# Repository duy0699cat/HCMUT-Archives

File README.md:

# HCMUT-Archives
llaalalala
a;dsuigflaisubgila

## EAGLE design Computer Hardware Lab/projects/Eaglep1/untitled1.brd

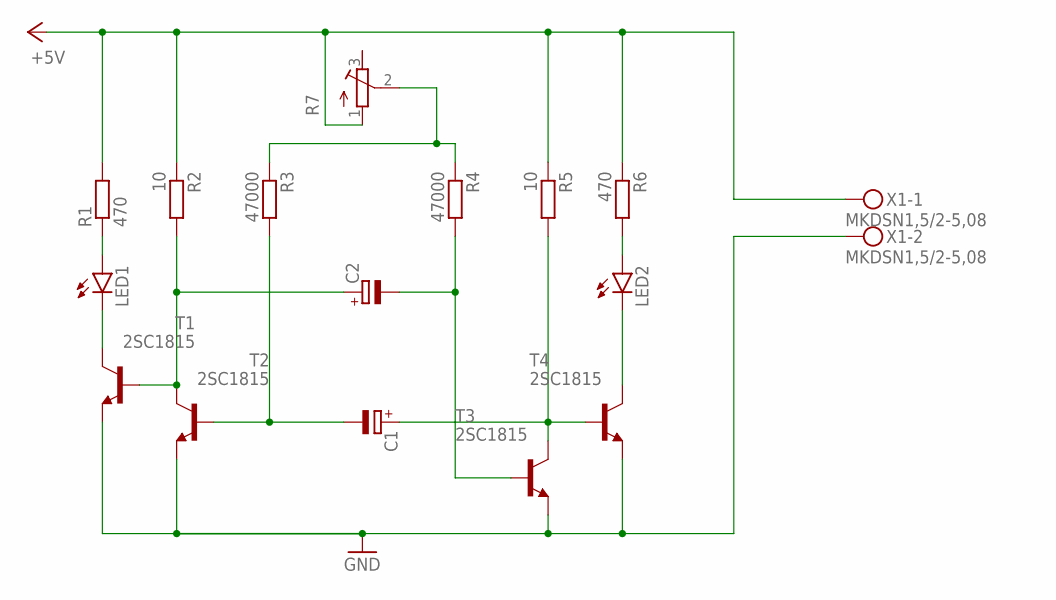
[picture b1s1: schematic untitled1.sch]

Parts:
C1, C2: CPOL-EUE3.5-8; E3,5-8
LED1, LED2: LED5MM
R1, R6: 470; 0309/12
R2, R5: 10; 0309/12
R3, R4: 47000; 0309/12
R7: R-TRIMM74X; RTRIM74X
T1, T2, T3, T4: 2SC1815; TO92-ECB
X1: MKDSN1,5/2-5,08

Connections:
+5V: R1.2, R2.1, R5.1, R6.1, R7.1 (A), X1.1
GND: T1.E, T2.E, T3.E, T4.E, X1.2
unnamed: R3.1, R4.1, R7.2 (S)
unnamed: LED2.A, R6.2
unnamed: LED1.A, R1.1
unnamed: LED1.K (C), T1.C
unnamed: C2.+, R2.2, T1.B, T2.C
unnamed: C1.-, R3.2, T2.B
unnamed: C2.-, R4.2, T3.B
unnamed: C1.+, R5.2, T3.C, T4.B
unnamed: LED2.K (C), T4.C

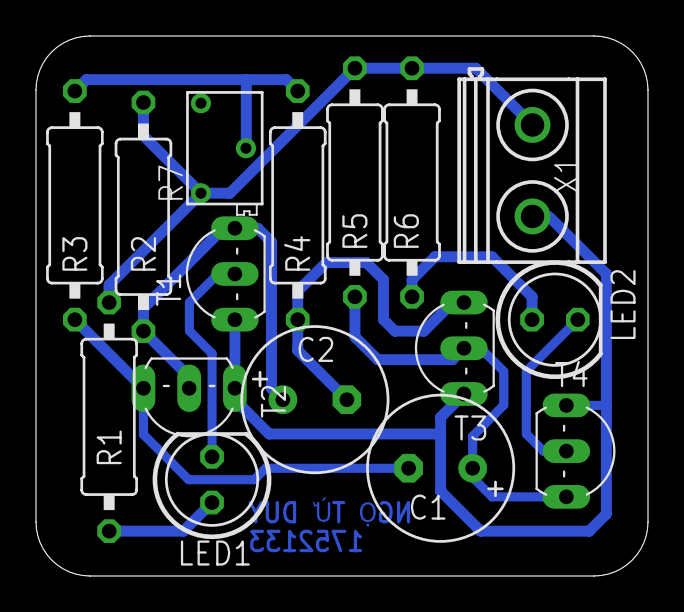
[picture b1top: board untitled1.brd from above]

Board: 2 copper layers, 34.0 x 30.0 mm, 16 parts (0 on the bottom side), 11 nets.

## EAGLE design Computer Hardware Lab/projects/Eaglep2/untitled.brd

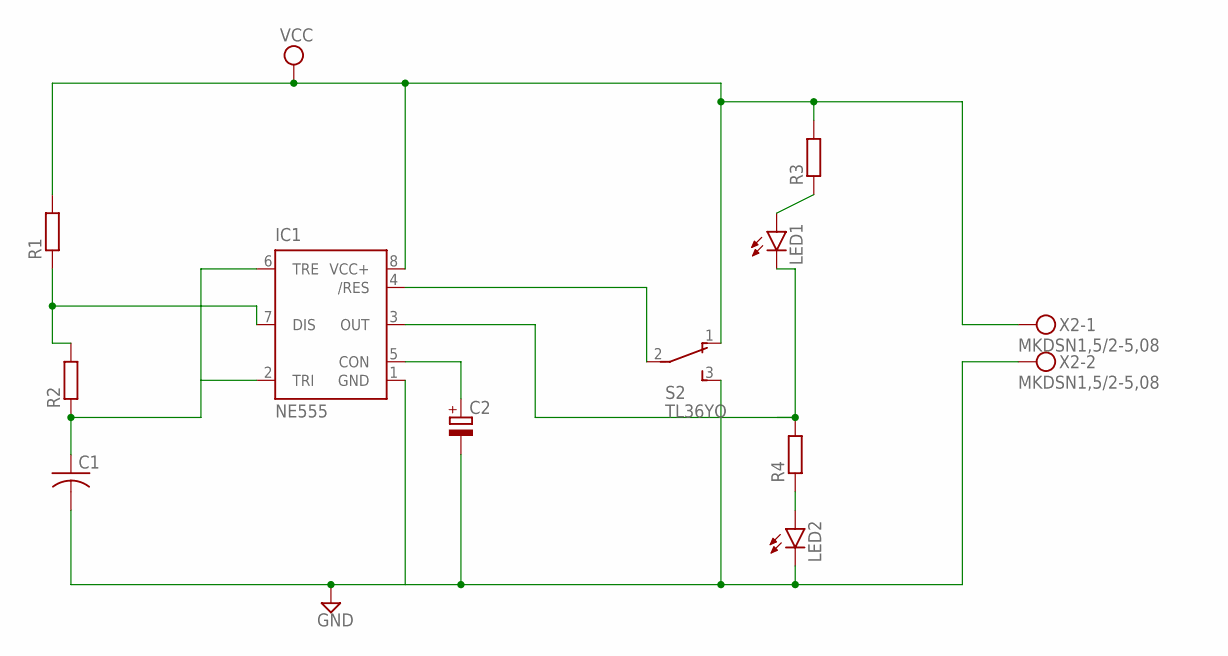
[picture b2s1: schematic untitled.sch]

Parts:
C1: C-US025-025X050; C025-025X050
C2: CPOL-EUE3.5-8; E3,5-8
IC1: NE555; DIL-08
LED1, LED2: LED5MM
R1, R2, R3, R4: R-EU_0309/12; 0309/12
S2: TL36YO; TL3XYO
X2: MKDSN1,5/2-5,08

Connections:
GND: C1.2, C2.-, IC1.1 (GND), LED2.K (C), S2.3 (S), X2.2
unnamed: IC1.7 (DIS), R1.1, R2.2
unnamed: C1.1, IC1.2 (TRI), IC1.6 (TRE), R2.1
unnamed: C2.+, IC1.5 (CON)
unnamed: LED2.A, R4.1
unnamed: IC1.3 (OUT), LED1.K (C), R4.2
unnamed: IC1.4 (/RES), S2.2
unnamed: LED1.A, R3.1
VCC: IC1.8 (VCC+), R1.2, R3.2, S2.1 (O), X2.1

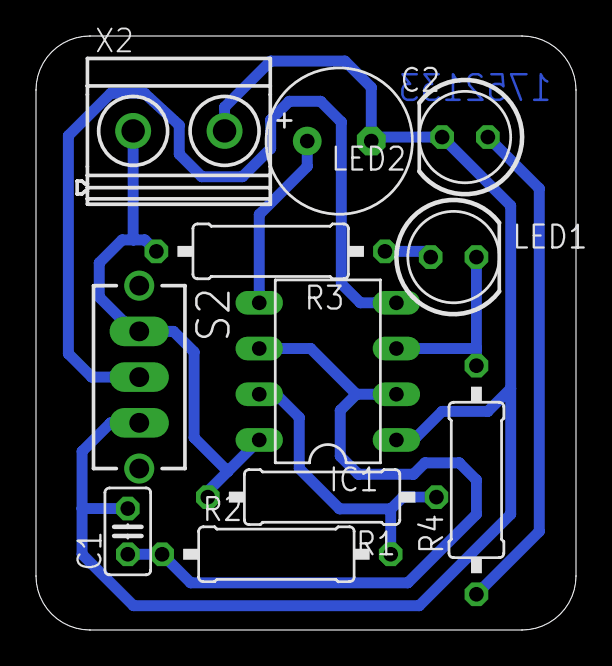
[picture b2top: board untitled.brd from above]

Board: 2 copper layers, 30.0 x 33.0 mm, 11 parts (0 on the bottom side), 9 nets.

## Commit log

2021-05-25 add project
2021-05-26 add prj
2021-07-01 update prj
2021-09-28 make prj
2021-10-12 auto update?
2021-11-17 add midterm
2022-07-05 add project (KTLT)
2023-06-10 Created using Colaboratory
